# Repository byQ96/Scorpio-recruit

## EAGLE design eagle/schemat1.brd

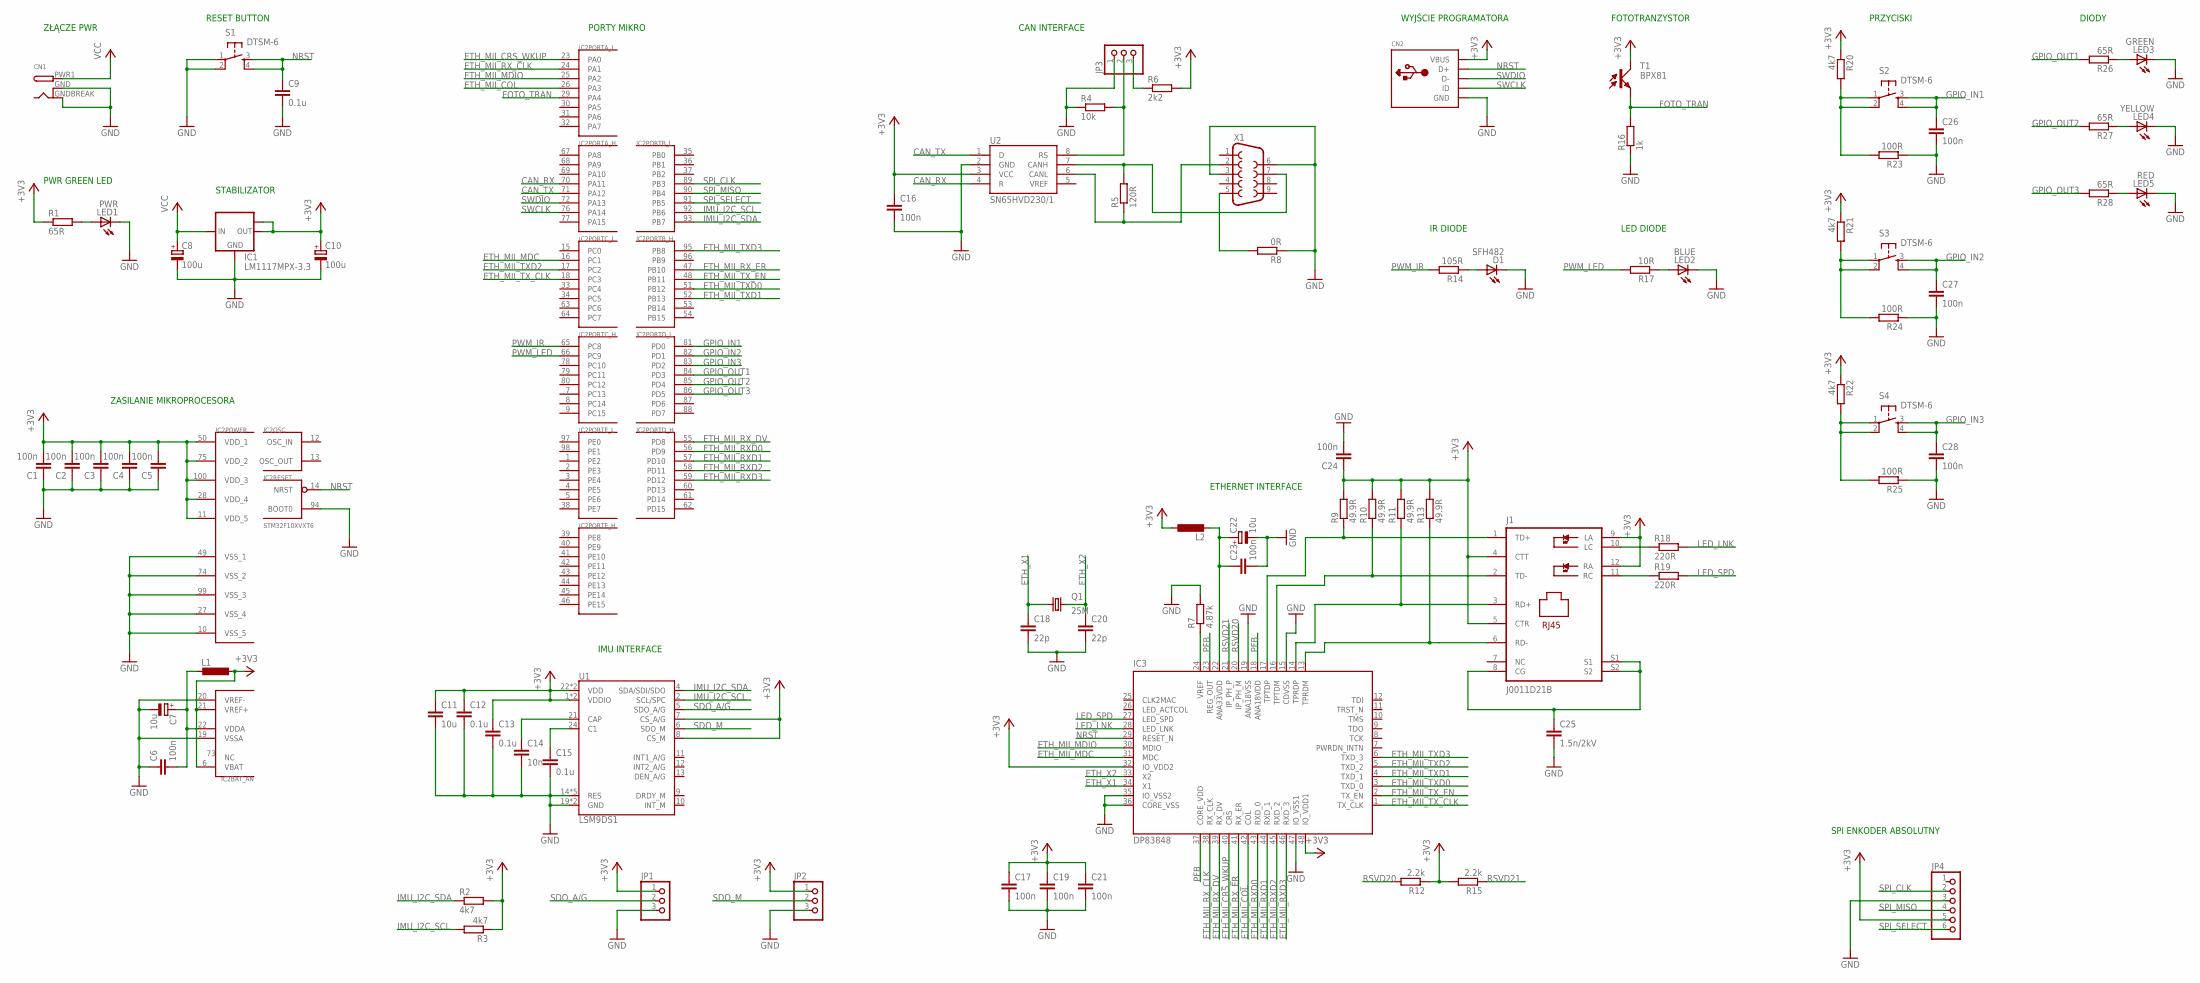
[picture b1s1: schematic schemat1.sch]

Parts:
C1, C2, C3, C4, C5, C6, C16, C17, C19, C21, C23, C24, C26, C27, C28: 100n; C0805
C7, C22: 10u; PANASONIC_C
C8, C10: 100u; PANASONIC_C
C9, C12, C13, C15: 0.1u; C0805
C11: 10u; C0805
C14: 10n; C0805
C18, C20: 22p; C0805
C25: 1.5n/2kV; C050-030X075
CN1: DCBARRELSMT; DCJACK_2MM_SMT
CN2: USBMINIB; USB-MINIB
D1: SFH482
IC1: LM1117MPX-3.3; SOT223
IC2: STM32F10XVXT6; TQFP100
IC3: DP83848; LQFP48
J1: J0011D21B; J0-A/B/F
JP1, JP2, JP3: PINHD-1X3; 1X03
JP4: PINHD-1X6/90; 1X06/90
L1, L2: L-EUL3230M; L3230M
LED1: PWR; CHIPLED_0805
LED2: BLUE; LED5MM
LED3: GREEN; CHIPLED_0805
LED4: YELLOW; CHIPLED_0805
LED5: RED; CHIPLED_0805
Q1: 25M; 3.2X2.5_KX-7
R1: 65R; R0805
R2, R3: 4k7; M0805
R4: 10k; M0805
R5: 120R; M0805
R6: 2k2; M0805
R7: 4,87k; R0805
R8: 0R; R0805
R9, R10, R11, R13: 49.9R; R0805
R12, R15: 2.2k; R0805
R14: 105R; M0805
R16: 1k; R0805
R17: 10R; M0805
R18, R19: 220R; R0805
R20, R21, R22: 4k7; R0805
R23, R24, R25: 100R; R0805
R26, R27, R28: 65R; M0805
S1, S2, S3, S4: DTSM-6
T1: BPX81
U1: LSM9DS1; LGA24-8X4
U2: SN65HVD230/1; SO8
X1: F09HP

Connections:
+3V3: C1.2, C2.2, C3.2, C4.2, C5.2, C10.+, C11.1, C12.1, C13.1, C16.1, C17.1, C19.1, C21.1, C24.1, CN2.VBUS, IC1.2 (OUT), IC1.TAB (OUT1), IC2.6 (VBAT), IC2.11 (VDD_5), IC2.21 (VREF+), IC2.28 (VDD_4), IC2.50 (VDD_1), IC2.75 (VDD_2), IC2.100 (VDD_3), IC3.32 (IO_VDD2), IC3.48 (IO_VDD1), J1.4 (CTT), J1.5 (CTR), J1.9 (LA), J1.12 (RA), JP1.1, JP2.1, JP4.5, L1.1, L2.1, R1.1, R2.2, R3.1, R6.2, R9.2, R10.2, R11.2, R12.1, R13.2, R15.2, R20.1, R21.1, R22.1, T1.C, U1.1 (VDDIO), U1.3 (VDDIO), U1.7 (CS_A/G), U1.8 (CS_M), U1.22 (VDD), U1.23 (VDD), U2.3 (VCC)
CAN_RX: IC2.70 (PA11), U2.4 (R)
CAN_TX: IC2.71 (PA12), U2.1 (D)
ETH_MII_COL: IC2.26 (PA3), IC3.42 (COL)
ETH_MII_CRS_WKUP: IC2.23 (PA0), IC3.40 (CRS)
ETH_MII_MDC: IC2.16 (PC1), IC3.31 (MDC)
ETH_MII_MDIO: IC2.25 (PA2), IC3.30 (MDIO)
ETH_MII_RXD0: IC2.56 (PD9), IC3.43 (RXD_0)
ETH_MII_RXD1: IC2.57 (PD10), IC3.44 (RXD_1)
ETH_MII_RXD2: IC2.58 (PD11), IC3.45 (RXD_2)
ETH_MII_RXD3: IC2.59 (PD12), IC3.46 (RXD_3)
ETH_MII_RX_CLK: IC2.24 (PA1), IC3.38 (RX_CLK)
ETH_MII_RX_DV: IC2.55 (PD8), IC3.39 (RX_DV)
ETH_MII_RX_ER: IC2.47 (PB10), IC3.41 (RX_ER)
ETH_MII_TXD0: IC2.51 (PB12), IC3.3 (TXD_0)
ETH_MII_TXD1: IC2.52 (PB13), IC3.4 (TXD_1)
ETH_MII_TXD2: IC2.17 (PC2), IC3.5 (TXD_2)
ETH_MII_TXD3: IC2.95 (PB8), IC3.6 (TXD_3)
ETH_MII_TX_CLK: IC2.18 (PC3), IC3.1 (TX_CLK)
ETH_MII_TX_EN: IC2.48 (PB11), IC3.2 (TX_EN)
ETH_X1: C18.1, IC3.34 (X1), Q1.1
ETH_X2: C20.1, IC3.33 (X2), Q1.3 (2)
FOTO_TRAN: IC2.29 (PA4), R16.2, T1.E
GND: C1.1, C2.1, C3.1, C4.1, C5.1, C6.1, C7.-, C8.-, C9.2, C10.-, C11.2, C12.2, C13.2, C14.2, C15.2, C16.2, C17.2, C18.2, C19.2, C20.2, C21.2, C22.-, C23.2, C24.2, C25.2, C26.2, C27.2, C28.2, CN1.GND (GNDBREAK), CN1.GNDBREAK (GND), CN2.GND, D1.K (C), IC1.1 (GND), IC2.10 (VSS_5), IC2.19 (VSSA), IC2.20 (VREF-), IC2.27 (VSS_4), IC2.49 (VSS_1), IC2.74 (VSS_2), IC2.94 (BOOT0), IC2.99 (VSS_3), IC3.15 (CDVSS), IC3.19 (ANA18VSS), IC3.35 (IO_VSS2), IC3.36 (CORE_VSS), IC3.47 (IO_VSS1), JP1.3, JP2.3, JP3.1, JP4.3, LED1.C, LED2.K (C), LED3.C, LED4.C, LED5.C, R4.1, R7.2, R8.1, R16.1, R23.1, R24.1, R25.1, S1.1, S1.2, U1.14 (RES), U1.15 (RES), U1.16 (RES), U1.17 (RES), U1.18 (RES), U1.19 (GND), U1.20 (GND), U2.2 (GND), X1.3, X1.6
GPIO_IN1: C26.1, IC2.81 (PD0), S2.3, S2.4
GPIO_IN2: C27.1, IC2.82 (PD1), S3.3, S3.4
GPIO_IN3: C28.1, IC2.83 (PD2), S4.3, S4.4
GPIO_OUT1: IC2.84 (PD3), R26.2
GPIO_OUT2: IC2.85 (PD4), R27.2
GPIO_OUT3: IC2.86 (PD5), R28.2
IMU_I2C_SCL: IC2.92 (PB6), R3.2, U1.2 (SCL/SPC)
IMU_I2C_SDA: IC2.93 (PB7), R2.1, U1.4 (SDA/SDI/SDO)
LED_LNK: IC3.28 (LED_LNK), R18.2
LED_SPD: IC3.27 (LED_SPD), R19.2
unnamed: IC3.13 (TPRDM), J1.6 (RD-), R13.1
unnamed: R8.2, X1.5
unnamed: R5.1, U2.6 (CANL), X1.2
unnamed: JP3.2, R4.2, U2.8 (RS)
unnamed: R5.2, U2.7 (CANH), X1.7
unnamed: JP3.3, R6.1
unnamed: IC3.14 (TPRDP), J1.3 (RD+), R11.1
unnamed: IC3.16 (TPTDM), J1.2 (TD-), R10.1
unnamed: IC3.24 (VREF), R7.1
unnamed: IC3.17 (TPTDP), J1.1 (TD+), R9.1
unnamed: C6.2, C7.+, IC2.22 (VDDA), L1.2
unnamed: LED1.A, R1.2
unnamed: J1.10 (LC), R18.1
unnamed: J1.11 (RC), R19.1
unnamed: C15.1, U1.24 (C1)
unnamed: C14.1, U1.21 (CAP)
unnamed: D1.A, R14.1
unnamed: LED2.A, R17.1
unnamed: C25.1, J1.8 (CG), J1.S1, J1.S2
unnamed: R20.2, R23.2, S2.1, S2.2
unnamed: R21.2, R24.2, S3.1, S3.2
unnamed: R22.2, R25.2, S4.1, S4.2
unnamed: LED3.A, R26.1
unnamed: C22.+, C23.1, IC3.22 (ANA33VDD), L2.2
unnamed: LED4.A, R27.1
unnamed: LED5.A, R28.1
NRST: C9.1, CN2.D+, IC2.14 (NRST), IC3.29 (RESET_N), S1.3, S1.4
PFB: IC3.18 (ANA18VDD), IC3.23 (REG_OUT), IC3.37 (CORE_VDD)
PWM_IR: IC2.65 (PC8), R14.2
PWM_LED: IC2.66 (PC9), R17.2
RSVD20: IC3.20 (IP_PH_M), R12.2
RSVD21: IC3.21 (IP_PH_P), R15.1
SDO_A/G: JP1.2, U1.5 (SDO_A/G)
SDO_M: JP2.2, U1.6 (SDO_M)
SPI_CLK: IC2.89 (PB3), JP4.2
SPI_MISO: IC2.90 (PB4), JP4.4
SPI_SELECT: IC2.91 (PB5), JP4.6
SWCLK: CN2.ID, IC2.76 (PA14)
SWDIO: CN2.D-, IC2.72 (PA13)
VCC: C8.+, CN1.PWR1 (PWR), IC1.3 (IN)

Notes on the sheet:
STABILIZATOR
ZASILANIE MIKROPROCESORA
WYJŚCIE PROGRAMATORA
CAN INTERFACE
ETHERNET INTERFACE
IMU INTERFACE
RESET BUTTON
ZŁĄCZE PWR
PWR GREEN LED
PORTY MIKRO
IR DIODE
FOTOTRANZYSTOR
LED DIODE
SPI ENKODER ABSOLUTNY
PRZYCISKI
DIODY

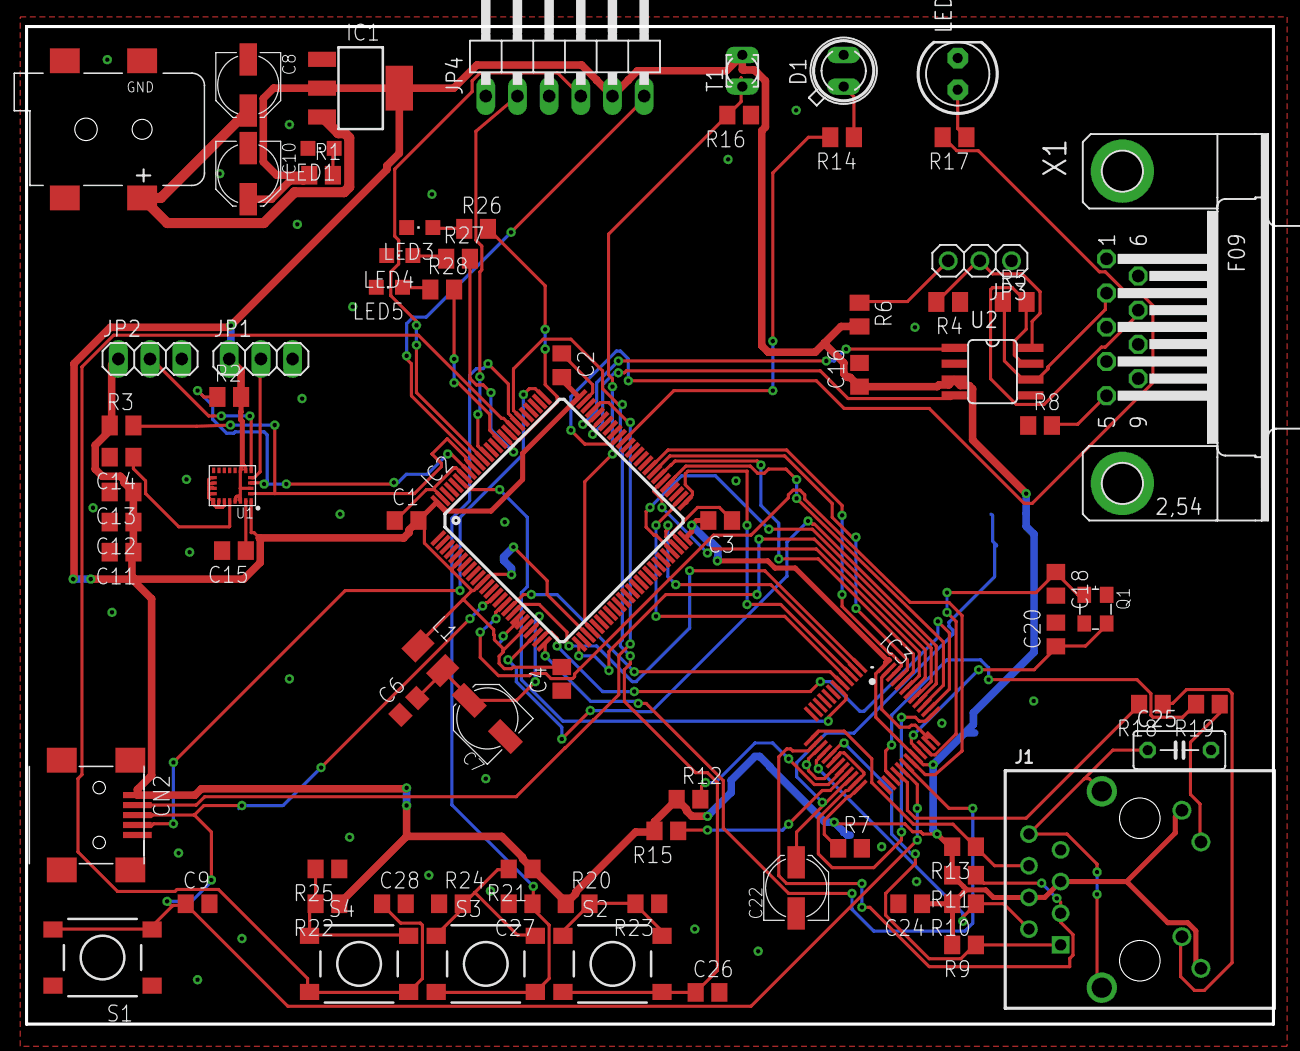
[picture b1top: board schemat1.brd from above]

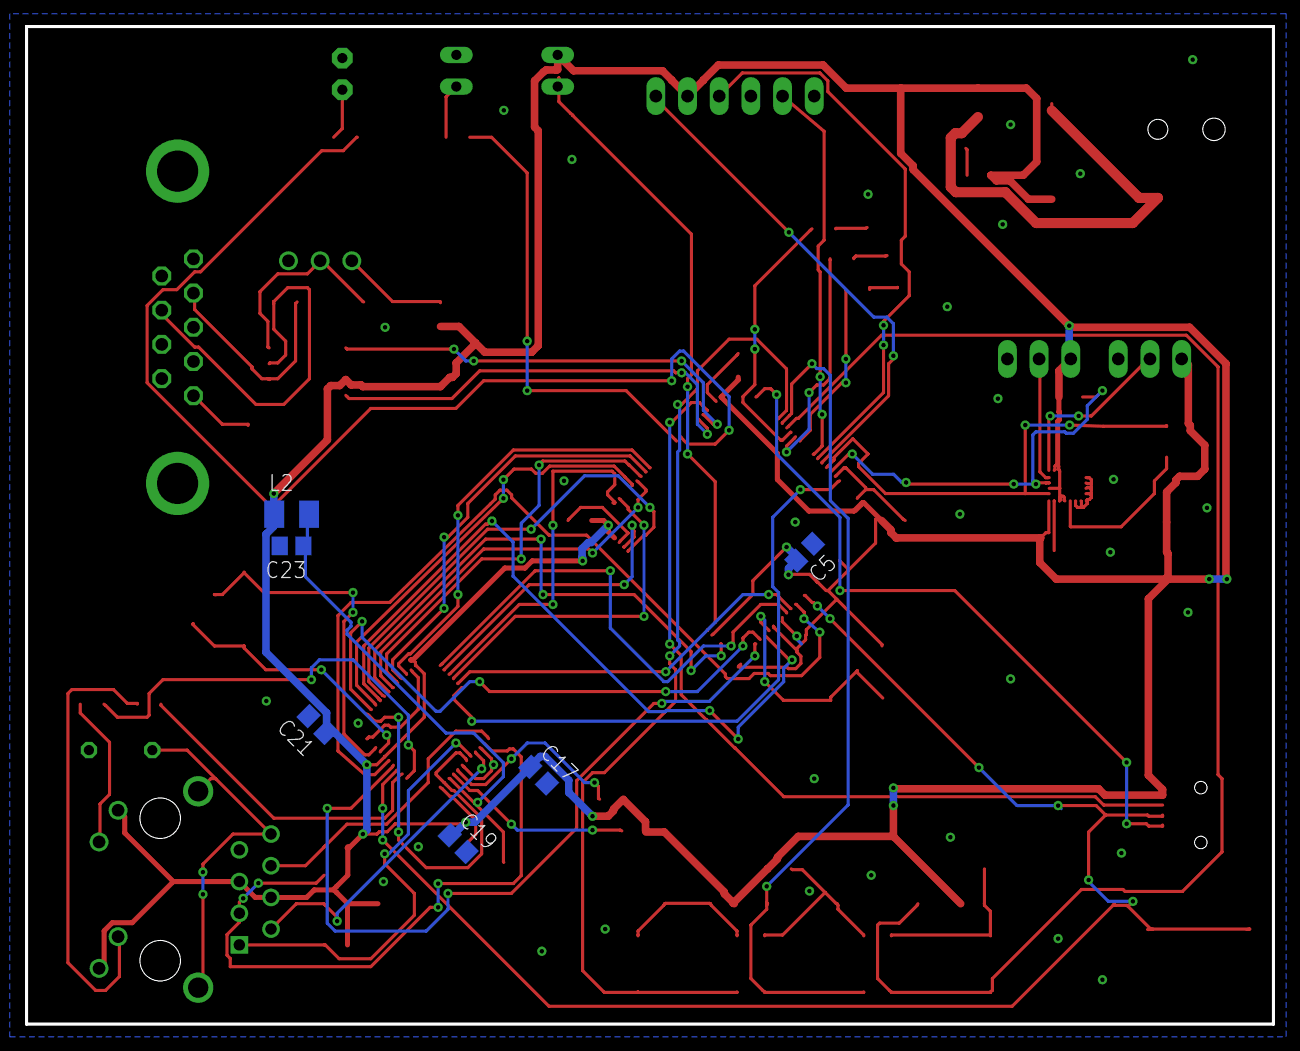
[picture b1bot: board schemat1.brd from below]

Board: 2 copper layers, 100.0 x 80.0 mm, 83 parts (6 on the bottom side), 74 nets.

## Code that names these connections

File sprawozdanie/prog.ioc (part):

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Mcu.Name=STM32F107V(B-C)Tx
Mcu.Package=LQFP100
Mcu.UserName=STM32F107VCTx
PA0-WKUP.Mode=MII
PA0-WKUP.Signal=ETH_CRS
PA1.Mode=MII
PA1.Signal=ETH_RX_CLK
PA11.Mode=Master
PA11.Signal=CAN1_RX
PA12.Mode=Master
PA12.Signal=CAN1_TX
PA2.Mode=MII
PA2.Signal=ETH_MDIO
PA3.Mode=MII
PA3.Signal=ETH_COL
PA4.GPIOParameters=GPIO_Label
PA4.GPIO_Label=FOTO_TRAN
PA4.Signal=ADCx_IN4
PB11.Mode=MII
PB11.Signal=ETH_TX_EN
PB12.Mode=MII
PB12.Signal=ETH_TXD0
PB13.Mode=MII
PB13.Signal=ETH_TXD1
PB3.Mode=RX_Only_Simplex_Unidirect_Master
PB3.Signal=SPI1_SCK
PB4.Mode=RX_Only_Simplex_Unidirect_Master
PB4.Signal=SPI1_MISO
PB5.GPIOParameters=GPIO_Label
PB5.GPIO_Label=SPI1_SELECT
PB5.Signal=GPIO_Input
PB6.Mode=I2C
PB6.Signal=I2C1_SCL
PB7.Mode=I2C
PB7.Signal=I2C1_SDA
PB8.Mode=MII
PB8.Signal=ETH_TXD3
PC1.Mode=MII
PC1.Signal=ETH_MDC
PC2.Mode=MII
PC2.Signal=ETH_TXD2
PC3.Mode=MII
PC3.Signal=ETH_TX_CLK
PC8.GPIOParameters=GPIO_Label
PC8.GPIO_Label=PWM_IR
PC8.Signal=S_TIM3_CH3
PC9.GPIOParameters=GPIO_Label
PC9.GPIO_Label=PWM_LED
PC9.Signal=S_TIM3_CH4
PD0.GPIOParameters=GPIO_Label
PD0.GPIO_Label=GPIO_IN1
PD0.Signal=GPIO_Input
PD1.GPIOParameters=GPIO_Label
PD1.GPIO_Label=GPIO_IN2
PD1.Signal=GPIO_Input
PD10.Mode=MII
PD10.Signal=ETH_RXD1
PD11.Mode=MII
PD11.Signal=ETH_RXD2
PD12.Mode=MII
PD12.Signal=ETH_RXD3
PD2.GPIOParameters=GPIO_Label
PD2.GPIO_Label=GPIO_IN3
PD2.Signal=GPIO_Input
PD3.GPIOParameters=GPIO_Label
PD3.GPIO_Label=GPIO_OUT1
PD3.Signal=GPIO_Output
PD4.GPIOParameters=GPIO_Label
PD4.GPIO_Label=GPIO_OUT2
PD4.Signal=GPIO_Output
PD5.GPIOParameters=GPIO_Label
PD5.GPIO_Label=GPIO_OUT3
PD5.Signal=GPIO_Output
PD8.Mode=MII
PD8.Signal=ETH_RX_DV
PD9.Mode=MII
PD9.Signal=ETH_RXD0
RCC.SYSCLKFreq_VALUE=26000000
RCC.SYSCLKSource=RCC_SYSCLKSOURCE_PLLCLK

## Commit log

2017-11-13 skonczone
2017-11-30 sprawozdanie+eagle

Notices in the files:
parts and their libraries:
pulse-eng: Copyright (C) 2008, Bob Starr
crystal-geyer_V1_0: Copyright: Geyer-Electronic
